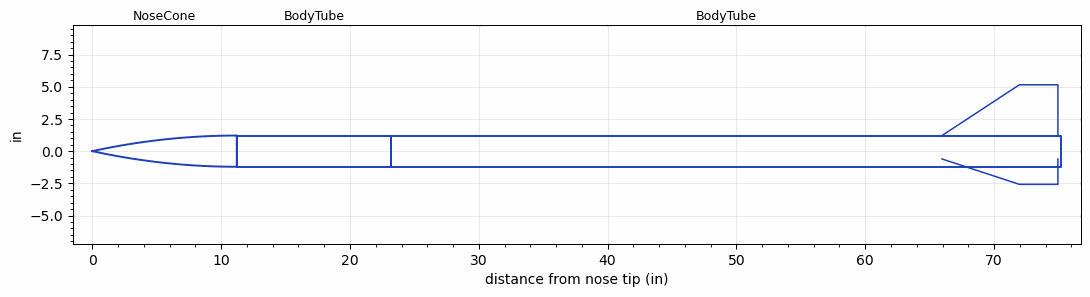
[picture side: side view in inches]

<RASAeroDocument>
 <FileVersion>2</FileVersion>
 <RocketDesign>
  <NoseCone>
   <Length>11.21</Length>
   <Diameter>2.424</Diameter>
   <Shape>Tangent Ogive</Shape>
   <Location>0</Location>
  </NoseCone>
  <BodyTube>
   <Length>12</Length>
   <Diameter>2.424</Diameter>
   <Location>11.21</Location>
  </BodyTube>
  <BodyTube>
   <Length>52</Length>
   <Diameter>2.424</Diameter>
   <Location>23.21</Location>
   <Fin>
    <Count>3</Count>
    <Chord>9</Chord>
    <Span>3.937</Span>
    <SweepDistance>6</SweepDistance>
    <TipChord>3</TipChord>
    <Thickness>0.15</Thickness>
    <Location>9.25</Location>
    <AirfoilSection>Hexagonal</AirfoilSection>
    <FX1>1</FX1>
    <FX3>1</FX3>
   </Fin>
  </BodyTube>
  <Surface>Smooth (Zero Roughness)</Surface>
  <ModifiedBarrowman>False</ModifiedBarrowman>
  <Turbulence>False</Turbulence>
  <UseBooster1>False</UseBooster1>
  <UseBooster2>False</UseBooster2>
 </RocketDesign>
 <LaunchSite>
  <Altitude>8904</Altitude>
  <Pressure>0</Pressure>
  <RodAngle>0</RodAngle>
  <RodLength>10</RodLength>
  <Temperature>68</Temperature>
  <WindSpeed>0</WindSpeed>
 </LaunchSite>
 <Recovery>
  <Altitude1>1000</Altitude1>
  <Altitude2>1000</Altitude2>
  <DeviceType1>None</DeviceType1>
  <DeviceType2>None</DeviceType2>
  <Event1>False</Event1>
  <Event2>False</Event2>
  <Size1>1</Size1>
  <Size2>1</Size2>
  <EventType1>None</EventType1>
  <EventType2>None</EventType2>
  <CD1>1.33</CD1>
  <CD2>1.33</CD2>
 </Recovery>
 <SimulationList>
  <Simulation>
   <SustainerEngine>L2050LW  (Loki)</SustainerEngine>
   <SustainerLaunchWt>14</SustainerLaunchWt>
   <SustainerNozzleDiameter>1</SustainerNozzleDiameter>
   <SustainerCG>45</SustainerCG>
   <SustainerIgnitionDelay>0</SustainerIgnitionDelay>
   <Booster1SeparationDelay>0</Booster1SeparationDelay>
   <Booster1IgnitionDelay>0</Booster1IgnitionDelay>
   <IncludeBooster1>False</IncludeBooster1>
   <Booster2Delay>0</Booster2Delay>
   <IncludeBooster2>False</IncludeBooster2>
   <TimetoApogee>41.02912</TimetoApogee>
   <MaxAltitude>35609.18</MaxAltitude>
   <MaxVelocity>2700.191</MaxVelocity>
  </Simulation>
 </SimulationList>
</RASAeroDocument>
